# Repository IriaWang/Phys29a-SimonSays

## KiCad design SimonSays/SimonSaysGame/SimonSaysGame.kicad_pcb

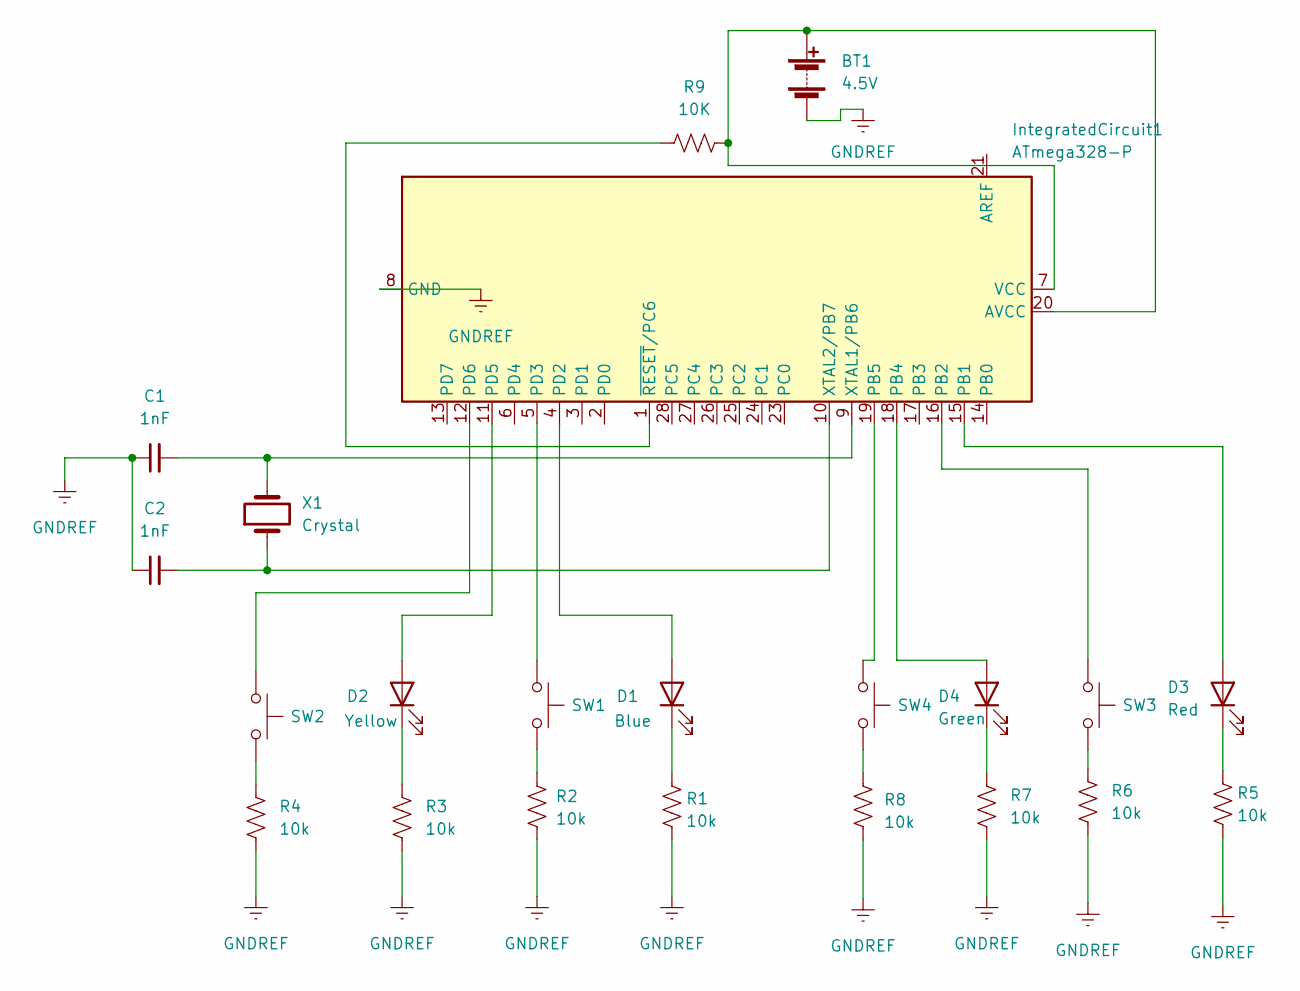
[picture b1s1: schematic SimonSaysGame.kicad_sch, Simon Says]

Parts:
BT1: 4.5V; BatteryHolder_Keystone_2479_3xAAA
C1, C2: 1nF; CP_Radial_D4.0mm_P1.50mm
D1: Blue; LED_D3.0mm
D2: Yellow; LED_D3.0mm
D3: Red; LED_D3.0mm
D4: Green; LED_D3.0mm
IntegratedCircuit1: ATmega328-P; DIP-28_W7.62mm
R1, R2, R3, R4, R5, R6, R7, R8: 10k; R_Axial_DIN0207_L6.3mm_D2.5mm_P7.62mm_Horizontal
R9: 10K; R_Axial_DIN0207_L6.3mm_D2.5mm_P7.62mm_Horizontal
SW1, SW2, SW3, SW4: SW_Push; SW_TH_Tactile_Omron_B3F-10xx
X1: Crystal; Crystal_HC49-4H_Vertical

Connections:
unnamed: BT1.1 (+), IntegratedCircuit1.7 (VCC), IntegratedCircuit1.20 (AVCC), R9.2
unnamed: C1.2, IntegratedCircuit1.9 (XTAL1/PB6), X1.2
unnamed: C2.2, IntegratedCircuit1.10 (XTAL2/PB7), X1.1
unnamed: D1.1 (K), R1.1
unnamed: D1.2 (A), IntegratedCircuit1.4 (PD2)
unnamed: D2.1 (K), R3.1
unnamed: D2.2 (A), IntegratedCircuit1.11 (PD5)
unnamed: D3.1 (K), R5.1
unnamed: D3.2 (A), IntegratedCircuit1.15 (PB1)
unnamed: D4.1 (K), R7.1
unnamed: D4.2 (A), IntegratedCircuit1.18 (PB4)
unnamed: IntegratedCircuit1.1 (~RESET/PC6), R9.1
unnamed: IntegratedCircuit1.5 (PD3), SW1.1
unnamed: IntegratedCircuit1.12 (PD6), SW2.1
unnamed: IntegratedCircuit1.16 (PB2), SW3.1
unnamed: IntegratedCircuit1.19 (PB5), SW4.1
unnamed: R2.1, SW1.2
unnamed: R4.1, SW2.2
unnamed: R6.1, SW3.2
unnamed: R8.1, SW4.2

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
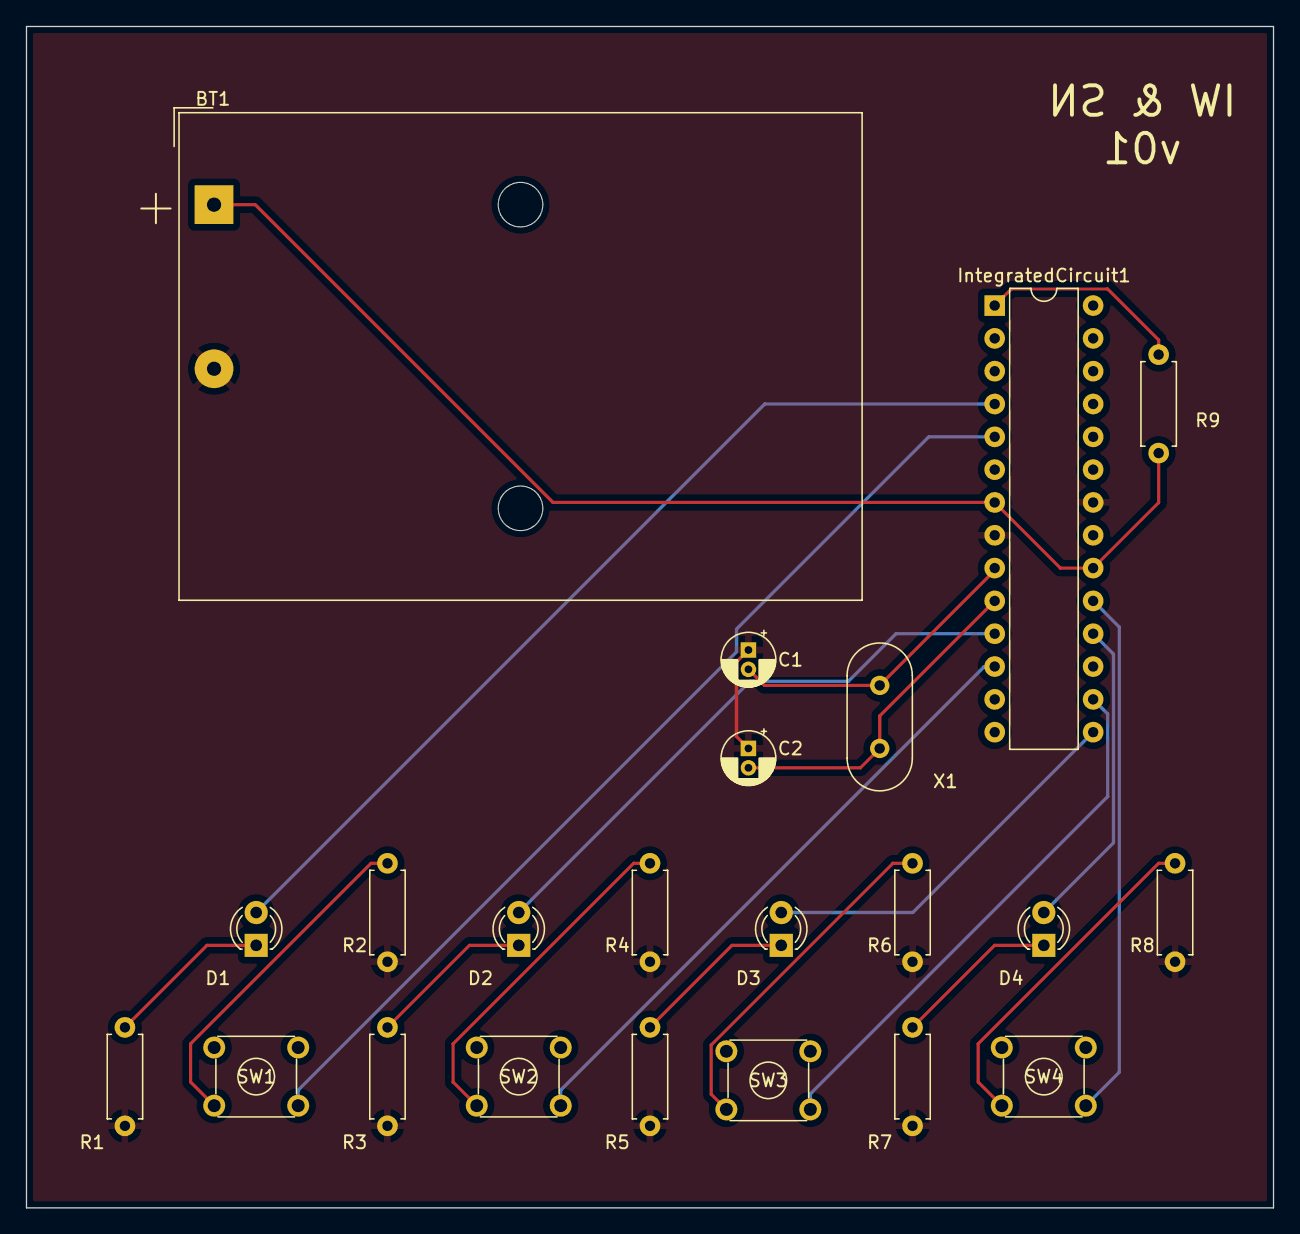
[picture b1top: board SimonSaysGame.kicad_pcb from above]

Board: 2 copper layers, 96.5 x 91.4 mm, 22 parts (0 on the bottom side), 21 nets.

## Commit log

2022-03-09 added KiCAD project
2022-03-09 added arduino code
2022-03-10 Added
2022-03-10 added .gitignore
2022-03-10 adde
2022-03-10 clean up wires
2022-03-10 clean footprints
2022-03-10 made new kicad project called Simon Says Game, Simon Says had problems updating the PCB
2022-03-10 finished PCB
2022-03-21 changed switches to tactile
2022-03-21 undo switch change
